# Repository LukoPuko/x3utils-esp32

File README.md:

# x3utils-esp32

A **standalone ESP32 flasher for the AT32F415 VCU** on X3-family e-scooters
(ZT3 Pro, Max G3, F3 / F3 Pro), controlled entirely from your **phone's browser
over WiFi**.

No PC. No ST-LINK. No app install. The ESP32 *is* the programmer: it bit-bangs
SWD to the scooter's debug pins itself, and hosts a web UI you drive from
Safari on an iPhone (or any browser — WiFi, so the Chrome/WebUSB limitation of
the original web app does not apply).

This is an ESP32 port of [**x3utils**](https://github.com/ztakis/x3utils). The
flashing *brains* — the AT32F415 erase/program/verify sequence, the FAP
read-protection check and rescue, the SHU-compatibility patch and its firmware
safety gates — are ported straight from the upstream engine. Only the transport
changed: an ESP32 GPIO SWD master replaces the ST-LINK, and a built-in web
server replaces the desktop GUI.

> [!WARNING]
> This tool writes the scooter VCU directly. A wrong file, a bad contact, or an
> interrupted flash can leave the controller unusable until recovered. **Always
> make a full backup first and keep it safe.** Use 3.3 V logic only, and power
> the VCU from **one** source at a time.

> [!IMPORTANT]
> **On-hardware validation status.** The firmware-identity / SHU-compat safety
> gates and the Thumb-2 version decoder are covered by host unit tests (see
> `host_test/`). The bit-banged SWD transaction layer (`swd.cpp`) follows the
> standard ADIv5 framing but has **not** been bench-verified against a real
> AT32F415 in this repository's CI (none exists). Treat your first connection as
> a bring-up: start with **Check connection** and **Backup**, confirm a clean
> 128 KB read, and only then flash. If you see `no ACK` / parity errors, raise
> the **SWD half-clock µs** setting (1–3) for a slower, more tolerant line.

---

## What it does

Same operations as the desktop/web app, from the browser:

- **Check connection** — read-only probe + target identification.
- **Backup 128 KB** — full dump, validated, downloaded to your phone as a `.bin`.
- **Backup + Flash** — upload a full 128 KB `.bin`; it erases, writes, verifies.
- **Flash slot 0** — upload a slot-0 `.bin` (identity-preserving).
- **Check protection** — read-only FAP (read-protection) verdict.
- **Unlock / Rescue** — clears FAP; this **mass-erases** main flash (recovery path).
- **Make SHU compatible** — dumps, patches the chip's own firmware at `0x1420`,
  and flashes it back. Safety-gated exactly like upstream: refuses non-factory
  firmware, XTEA-present (too-new) firmware, unsupported models (GT3), and
  blacklisted/unidentified versions.

Connection modes: **Default SWD**, **Under-reset (nRST)**, and **Power-race**
(hammer connect while you apply power).

---

## Hardware

### Option A — the X3-Tuner PCB (all-in-one)

[`hardware/`](hardware/) contains a ready-to-order board built only for this
job (documentation in German):
- **MCU:** ESP32-C3-WROOM-02 module, chosen as the cost-optimised option.
- **USB:** USB-C wired to the C3's native USB, so no USB-UART chip is needed.
- **Battery:** 1S LiPo with a TP4056 charger and DW01A protection.
- **VCU supply:** a GPIO-switched 3.3 V supply, so the firmware can run *Power-race* by itself.
- **Board:** 38 × 54.5 mm, two layers, all parts on one side.
- **Manufacturing files:** Gerber, BOM and CPL for JLCPCB assembly, plus a 10-up panel for volume orders.
- **Case:** a 3D-printable enclosure.

Build the firmware with `pio run -e x3tuner -t upload`.

### Option A2 — X3-Tuner Mini: carrier board for an ESP32-C3 SuperMini

[`hardware/carrier/`](hardware/carrier/) is a cheaper board: a ready-made
ESP32-C3 SuperMini (about 1.80 €) is pushed onto pin headers the factory solders
to the carrier and is held by the case lid. The carrier adds:
- a 1S LiPo charger with reverse-polarity protection, and an on/off switch;
- the switched VCU supply;
- battery, USB and VCU voltage sensing;
- the SWD header.

Every part is machine-assembled, nothing to solder. In volume a complete board
including the SuperMini comes to about 3.75 €. The board is a 20.5 × 65 mm
stick; with its 3D-printed case and a LiPo the device measures about
78 × 24 × 21 mm. The case is fully closed (no button holes) and the firmware can
be locked against readout with Wi-Fi-only OTA updates — see
[hardware/carrier/SECURITY.md](hardware/carrier/SECURITY.md). Build the firmware
with `pio run -e x3carrier -t upload`.

### Option B — any ESP32 dev board

- An **ESP32** board (classic ESP32, or an S3 / C3 — see `platformio.ini`).
- Four wires to the scooter's debug header: **SWCLK**, **SWDIO**, **GND**, and
  **nRST / C45** (strongly recommended — needed for Under-reset mode and most
  reliable for locked/running targets).
- A 3.3 V power path for the VCU (bench/main power **or** the ESP32 3V3 pin —
  never both). See the upstream wiki's per-model guides for pad locations and
  the C45 point.

### Default pin map (classic ESP32 — change in `src/config.h` or the UI)

| Signal | GPIO |
|--------|------|
| SWCLK  | 18   |
| SWDIO  | 19   |
| nRST   | 21   |
| GND    | any GND |

S3/C3 defaults are different — see `src/config.h`.

---

## Build & flash the ESP32

Uses [PlatformIO](https://platformio.org/).

```bash
# classic ESP32
pio run -e esp32dev -t upload

# or an S3 / C3 board
pio run -e esp32-s3 -t upload
# the X3-Tuner PCB from hardware/ (ESP32-C3, native USB)
pio run -e x3tuner -t upload
# the X3-Tuner Mini carrier from hardware/carrier/ with a plug-in SuperMini
pio run -e x3carrier -t upload
pio run -e esp32-c3 -t upload

# watch the serial log (shows the WiFi IP)
pio device monitor -b 115200
```

First boot creates a **WiFi hotspot**:

- SSID: `x3utils-esp32`  ·  password: `x3utils123`
- Join it from your phone, then open **http://192.168.4.1/** (or
  **http://x3utils.local/**).

To join your own network instead, open **Settings → WiFi → Join network** in the
UI, enter your SSID/password, and save (the ESP32 reboots and connects; find its
IP on the serial monitor or your router).

---

## Using it from your phone

1. Wire SWCLK / SWDIO / GND / nRST to the VCU, power the VCU from one source.
2. Join the ESP32 hotspot and open the page.
3. Pick a connection mode (start with **Default SWD**; use **Under-reset** if the
   firmware keeps SWD disabled while running).
4. **Check connection** → you should see the AT32F415 part identified.
5. **Backup 128 KB** → wait for "Backup complete", then **Download last backup**.
6. Only now flash: **Backup + Flash** / **Flash slot 0** (upload a `.bin`), or
   **Make SHU compatible**.

The console streams live log + progress over a WebSocket. **Abort** stops a
running operation (safe between steps; a flash in progress finishes its current
word).

---

## How the port works

The upstream engine is written against a tiny debug-probe surface — read/write a
debug register, read/write memory, drive nRST. `src/swd.cpp` provides exactly
that surface by bit-banging ADIv5 SWD on two GPIOs, so the AT32 flash algorithm
in `src/at32.cpp` is the *same* algorithm the desktop/web app runs:

```
browser ──HTTP/WebSocket──> ESP32 web server (main.cpp)
                                  │  queues one command
                                  ▼
                            x3_ops.cpp  (Check/Backup/Flash/Compat/Protection)
                                  │
                      at32.cpp (Cortex-M + AT32F415 flash)   fw_ident.cpp (SHU gates)
                                  │
                              swd.cpp  (bit-banged ADIv5 SWD)
                                  │  SWCLK / SWDIO / nRST
                                  ▼
                           AT32F415 VCU
```

The experimental SRAM flash loader from upstream is intentionally **not** ported;
this uses the field-proven direct word-write path. The SHU-compat patch,
factory-state check, XTEA gate, model allow-list, and the Thumb-2 version
blacklist/known-version decoder are ported faithfully in `src/fw_ident.cpp`.

### Source layout

```
src/
  config.h       pins, WiFi defaults, SWD timing, target geometry
  swd.{h,cpp}    bit-banged ADIv5 SWD master (the ST-LINK replacement)
  at32.{h,cpp}   Cortex-M debug + AT32F415 detect / erase / program / verify / FAP
  fw_ident.{h,cpp}  banner, factory-state, version matrix, SHU-compat gates
  x3_ops.{h,cpp} high-level operations driven by the UI
  web_ui.h       the mobile web UI (served from flash)
  main.cpp       WiFi + web server + WebSocket + routing + settings
host_test/            host unit tests for the safety gates (see below)
```

## Tests

The portable safety-critical logic has host-side unit tests (no hardware, no
ESP toolchain needed):

```bash
cd host_test
g++ -std=gnu++17 -I shim -I ../src test_fwident.cpp ../src/fw_ident.cpp -o t && ./t
```

They cover the Thumb-2 version decoder, the blacklist floor, the XTEA / factory
/ already-compatible / unidentified refusals, the MCU model requirement, and the
16-byte compat patch.

---

## Credits & license

MIT. Ported from [x3utils](https://github.com/ztakis/x3utils) (© ztakis) and its
swdart engine (© nopbxlr). See [LICENSE](LICENSE). Supported models and the
firmware version matrix mirror upstream; consult the upstream wiki for wiring,
C45 locations, and SHU-compat firmware limits.

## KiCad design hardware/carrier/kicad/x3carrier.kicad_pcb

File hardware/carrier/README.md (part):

# X3-Tuner Mini – Trägerplatine für das ESP32-C3 SuperMini

Die günstige Variante des X3-Tuners, als schmaler **Stick** mit 3D-Druck-Gehäuse
(ca. 78 × 24 × 21 mm). Den ESP32 kaufst du als fertiges **ESP32-C3 SuperMini**
(ca. 1,80 €) und **steckst ihn einfach auf**. Das SuperMini hat **keine
eingelöteten Stifte** – die sitzen auf der Trägerplatine, die Fabrik lötet sie
an, und das SuperMini wird draufgesteckt und vom Deckel festgehalten.
Die Trägerplatine bringt alles mit, was dem SuperMini fehlt:

- 1S-LiPo-Akku mit TP4056-Ladeschaltung, geladen über die USB-C-Buchse des SuperMini
- Verpolschutz für den Akku (viele Billig-Akkus haben vertauschte Kabel)
- Ein/Aus-Schiebeschalter
- schaltbare 3,3-V-Versorgung für die Scooter-VCU (Power-Race per Firmware)
- Messung von Akku, USB und VCU-Spannung
- SWD-Stiftleiste zum Scooter

**Du lötest nichts.** Die Fabrik bestückt alle Teile, auch die beiden
Stiftleisten für das SuperMini und die SWD-Stiftleiste.

> [!NOTE]
> **Geschlossenes Gehäuse, geschützte Firmware.** Es gibt keine Öffnungen für
> die RESET-/BOOT-Taster: Niemand kommt von außen an das SuperMini. Die Firmware
> kann so eingestellt werden, dass sie **nicht ausgelesen oder über USB
> umgeflasht** werden kann und Updates **nur per WLAN über deine App** laufen –
> siehe [SECURITY.md](SECURITY.md).

| Gehäuse | Durchsichtig (Aufbau) |
|---|---|
|  |  |
| **Schnitt** | **Explosionsansicht** |
|  |  |

| Platine oben | Platine unten |
|---|---|
|  |  |

[Schaltplan (PDF)](docs/x3carrier-schematic.pdf) ·
[Bestückungsplan (PDF)](docs/x3carrier-assembly.pdf) ·
[Fertigungsdaten](production/) ·
[Gehäuse (STL)](case/stl/)

> [!IMPORTANT]
> **Status: Design fertig (Rev. 1.2, Stick mit Stiftleisten), noch nicht
> gefertigt.** DRC: 0 Fehler, 0 offene Verbindungen, der Schaltplan wird
> automatisch gegen die Netzliste geprüft. Das Gehäuse ist gegen Platine,
> SuperMini und Akku auf Kollisionen geprüft. **Eine Sache fehlt noch:** die
> LCSC-Nummer der 1×8-Stiftleiste – siehe [Bestellen](#bestellen). Vor der
> Bestellung bitte [diese Punkte](#vor-der-bestellung-prüfen) prüfen.

## Was drauf ist

| Block | Lösung |
|---|---|
| Platine | 20,5 × 65 mm, 2 Lagen, alle Teile oben |
| ESP32 | ESP32-C3 SuperMini, auf 2 × 1×8-**Stiftleisten** (2,54 mm) aufgesteckt und vom Deckel niedergehalten, USB-C an der vorderen Kante |
| Laden | TP4056, ca. 235 mA, gespeist aus dem 5V-Pin des SuperMini (= USB VBUS). LEDs: rot = lädt, grün = voll |
| Akku | 1S LiPo **mit eigener Schutzschaltung**, JST-PH-2.0-Buchse, Verpolschutz (P-MOSFET Q3) |
| Ein/Aus | Schiebeschalter MSK12C02. Er schaltet nur das Gate des P-MOSFET Q1 und trägt keinen Laststrom |
| Akkubetrieb | Akku → Q3 → Q1 → Schottky-Diode D1 → 5V-Pin → 3,3-V-Regler des SuperMini |
| VCU-Versorgung | P-MOSFET Q2 aus 3V3 des SuperMini, GPIO7 low = an, beim Booten aus |
| SWD | gewinkelte 1×5-Stiftleiste an der hinteren Kante (3V3 · DIO · CLK · RST · GND), 100 Ω Serienwiderstände |

### Belegung des SuperMini

Ansicht von oben, USB-C nach oben. Pin 1 jeder Reihe ist der Pin neben USB-C.
Auf der Platine zeigt USB-C zur vorderen Kante (Aufdruck „USB-C“), die
5V-Reihe liegt dann links (Aufdruck „5V“).

| Linke Reihe | Funktion | Rechte Reihe | Funktion |
|---|---|---|---|
| 5V | Akku / Lader (= USB VBUS) | GPIO5 | SWDIO |
| GND | GND | GPIO6 | nRST |
| 3V3 | 3,3 V für die VCU | GPIO7 | VCU-Versorgung ein (low) |
| GPIO4 | SWCLK | GPIO8 | blaue LED des SuperMini (Status, im Gehäuse verdeckt) |
| GPIO3 | VCU-Spannung messen | GPIO9 | BOOT-Taster (im Gehäuse nicht erreichbar) |
| GPIO2 | frei (Strapping) | GPIO10 | frei |
| GPIO1 | USB-Erkennung | GPIO20 | frei |
| GPIO0 | Akkuspannung messen | GPIO21 | frei |

SWD liegt auf denselben Pins wie beim nackten SuperMini (Firmware-Umgebung
`esp32-c3`). Die Trägerplatine hat ein eigenes Firmware-Profil:

```bash
pio run -e x3carrier -t upload
```

### Stromversorgung

- **USB eingesteckt:** USB versorgt das SuperMini, der TP4056 lädt den Akku.
  D1 sperrt, deshalb wird der Akku nur geladen und nicht gleichzeitig belastet.
  Laden funktioniert auch bei ausgeschaltetem Schalter. Das SuperMini läuft dann
  über USB trotzdem.
- **Akku:** Schalter auf EIN, dann versorgt der Akku das SuperMini über Q3, Q1 und D1.
  Durch die Diode und den Regler des SuperMini sinkt die 3,3-V-Schiene ab etwa
  3,5 V Akkuspannung. Das Gerät geht dann früher aus als mit einem eigenen
  Regler, nutzbar sind ca. 85–90 % der Akkukapazität.
- **Aus:** Am Akku hängt nur der Messteiler mit 1 MΩ + 1 MΩ, das sind ca. 2 µA.
- **Akku verkehrt herum:** Q3 sperrt. Es geht nichts kaputt, das Gerät läuft
  nur nicht mit Akku und lädt ihn nicht.

## Akku

Ins Gehäuse passt ein Akku bis **21 × 33 × 7 mm**. Er liegt in einer Tasche
unter dem Deckel, über der Ladeschaltung. Gut passen die Größen 702030 und
602030. Die Zahl steht für Dicke, Breite und Länge: 602030 ist 6,0 × 20 × 30 mm.
Der Akku braucht eine **Schutzschaltung** und einen **JST-PH-2.0-Stecker**
(2 mm Raster). Beides ist bei Akkus mit Stecker üblich.

| Akku | Kapazität | Maße (L × B × D) | Polarität | Preis |
|---|---|---|---|---|
| [efaso 702030](https://www.amazon.de/dp/B0BK9JQY42) (Amazon.de, empfohlen) | 300 mAh | 30 × 20 × 7 mm | nicht angegeben, prüfen | ca. 9 € |
| [Pimoroni LiPo 150 mAh](https://botland.store/battery-li-pol-1s-37-v/21461-li-pol-battery-pimoroni-150mah-37v-jst-connector-27x205x43mm-0704256796549.html) | 150 mAh | 27 × 20,5 × 4,3 mm | passt garantiert (Adafruit-Belegung) | ca. 6 € |
| [Berrybase LP-402025](https://www.berrybase.de/en/lp-402025-lithium-polymer-lipo-battery-3.7v-150mah-with-2-pin-jst-connector) | 150 mAh | 26 × 20 × 4 mm | nicht angegeben, prüfen | ca. 3,30 € |

Die Akkutasche ist für Zellen bis **7 mm** Dicke ausgelegt. Ein dickerer 8-mm-Akku
(z. B. ein 802030, 400 mAh) würde sonst an die JST-Buchse stoßen; dafür den
Deckel 2 mm höher bauen (`CASE_TOP_CLEAR` in [`../gen/circuit_carrier.py`](../gen/circuit_carrier.py)
auf 15 setzen und neu rendern).

Mit 300 mAh läuft das Gerät mit WLAN ca. 2–3 Stunden, mit 150 mAh gut eine
Stunde. Für einen Flash-Vorgang reicht beides. Der Ladestrom von ca. 235 mA
passt gut zu 300 mAh. Für die 150-mAh-Akkus ist er etwas hoch (1,5C), sie altern
dadurch schneller.

**Zwei kleine Akkus parallel** sind keine gute Idee: Sind sie beim Zusammenstecken
unterschiedlich voll, fließt ein großer Ausgleichsstrom, den nichts begrenzt.
Außerdem bräuchtest du ein Y-Kabel, und das müsste man löten. Ein einzelner
702030 hat mehr Kapazität als zwei 150-mAh-Zellen und passt in dasselbe Fach.

**Polarität:** Die Platine hat die Belegung von Adafruit und SparkFun:
**+ (rot) an Pin 1**. Schau in die Öffnung der Buchse, die Platine liegt unten.
Dann ist + **links**, daneben steht „+“ auf der Platine. Am Akkustecker gilt:
Schau auf die Kontaktöffnungen, die Rastnase zeigt nach oben. Dann muss Rot
**rechts** sein. Bei Akkus von Amazon und AliExpress ist das oft vertauscht.
Steckst du so einen Akku an, sperrt der Verpolschutz und es passiert nichts.
Umbauen geht auch ohne Löten: Hebe mit einer Nadel die kleine Rastzunge über
einem Kontakt im Steckergehäuse an. Dann kannst du das Kabel samt Kontakt
herausziehen. Beide Kabel tauschen und wieder einrasten.

## Gehäuse

Facettierter Stick aus zwei Teilen, die ohne Schrauben einrasten.
Außenmaß **77,7 × 24,4 × 20,9 mm**. Die Oberseite ist geschlossen, nur die
Lade-LED zeigt sich durch einen schmalen Schlitz. Es nutzt dasselbe Modell wie
das [X3-Tuner-Gehäuse](../case/) ([`../case/case_core.scad`](../case/case_core.scad)).

| Ebene | Höhe |
|---|---|
| Boden | 1,2 mm |
| Luft für die Lötbeine der Stiftleisten (THT) | 3,2 mm |
| Platine | 1,6 mm |
| SuperMini auf den Stiftleisten (2,5 mm) + Luft, Akku im Deckel (bis 8 mm) | 13,5 mm |
| Deckel | 1,4 mm |
| **Gesamt** | **20,9 mm** |

Weil das SuperMini jetzt flach auf den Stiftleisten sitzt (statt auf hohen
Buchsen), bestimmt der **Akku im Deckel** die Höhe. Mit einem 7-mm-Akku bleibt
es bei 20,9 mm.

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
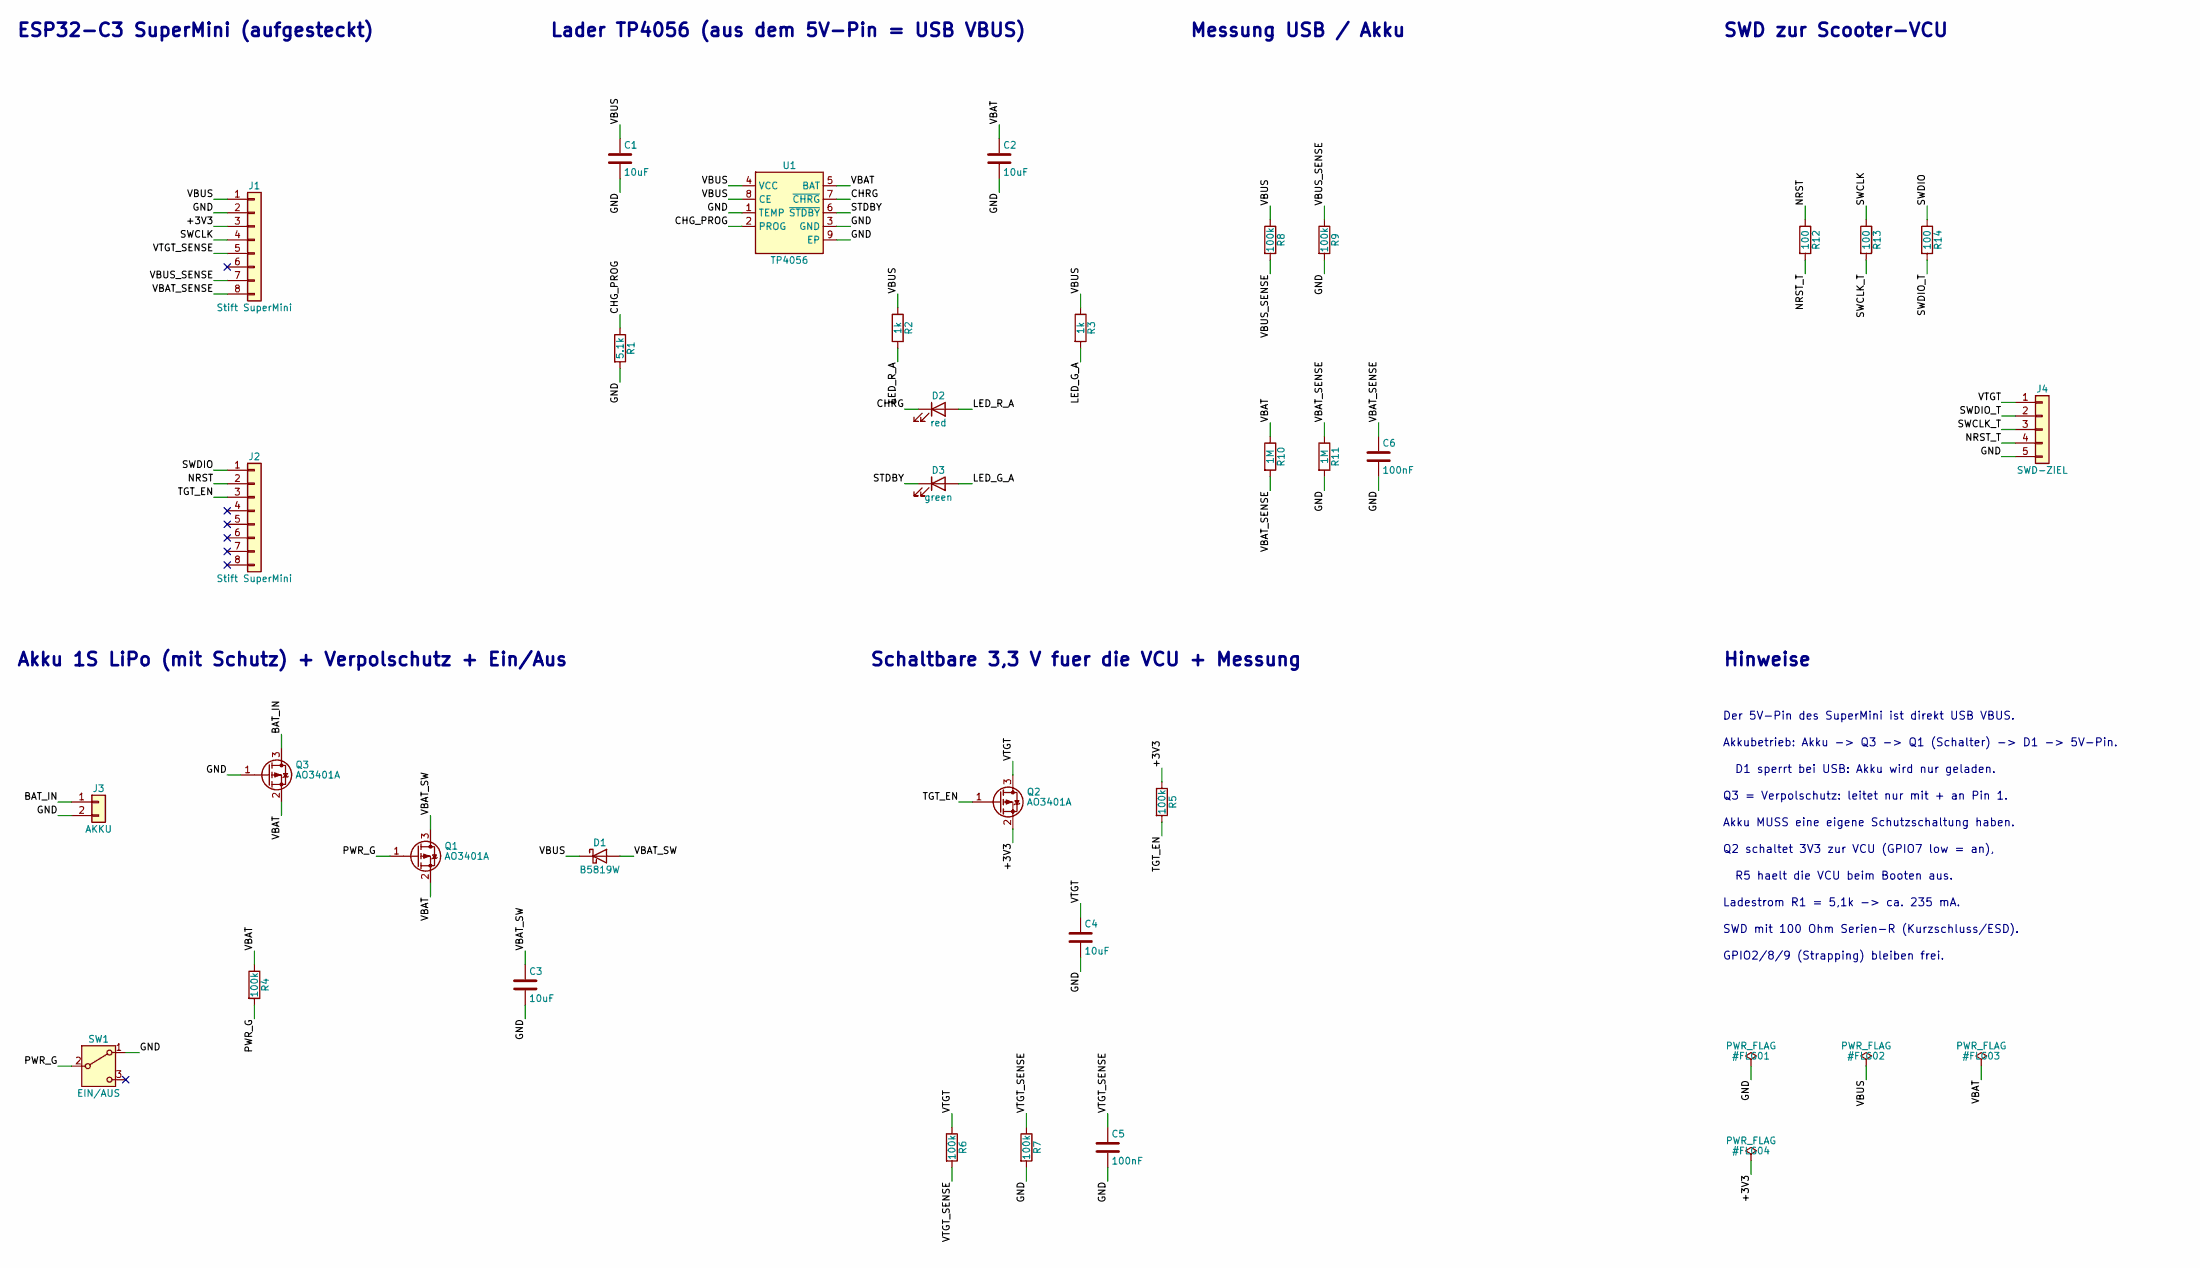
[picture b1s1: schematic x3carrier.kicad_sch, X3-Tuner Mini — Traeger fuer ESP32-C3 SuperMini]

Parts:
C1, C2, C3, C4: 10uF; C_0603_1608Metric; LCSC C19702
C5, C6: 100nF; C_0402_1005Metric; LCSC C1525
D1: B5819W; D_SOD-123; LCSC C8598
D2: red; LED_0603_1608Metric; LCSC C2286
D3: green; LED_0805_2012Metric; LCSC C2297
J1, J2: Stift SuperMini; PinHeader_1x08_P2.54mm_Vertical
J3: AKKU; JST_PH_S2B-PH-SM4-TB_1x02-1MP_P2.00mm_Horizontal; LCSC C295747
J4: SWD-ZIEL; PinHeader_1x05_P2.54mm_Horizontal; LCSC C32713264
Q1, Q2, Q3: AO3401A; SOT-23; LCSC C15127
R1: 5.1k; R_0402_1005Metric; LCSC C25905
R2, R3: 1k; R_0402_1005Metric; LCSC C11702
R4, R5, R6, R7, R8, R9: 100k; R_0402_1005Metric; LCSC C25741
R10, R11: 1M; R_0402_1005Metric; LCSC C26083
R12, R13, R14: 100; R_0402_1005Metric; LCSC C25076
SW1: EIN/AUS; SW_SPDT_MSK12C02; LCSC C431540
U1: TP4056; SOIC-8-1EP_3.9x4.9mm_P1.27mm_EP2.41x3.3mm; LCSC C16581

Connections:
+3V3: J1.3, Q2.2 (S), R5.1
BAT_IN: J3.1, Q3.3 (D)
CHG_PROG: R1.1, U1.2 (PROG)
CHRG: D2.1 (K), U1.7 (~CHRG)
GND: C1.2, C2.2, C3.2, C4.2, C5.2, C6.2, J1.2, J3.2, J4.5, Q3.1 (G), R1.2, R7.2, R9.2, R11.2, SW1.1 (A), U1.1 (TEMP), U1.3 (GND), U1.9 (EP)
LED_G_A: D3.2 (A), R3.2
LED_R_A: D2.2 (A), R2.2
NRST: J2.2, R12.1
NRST_T: J4.4, R12.2
PWR_G: Q1.1 (G), R4.2, SW1.2 (B)
STDBY: D3.1 (K), U1.6 (~STDBY)
SWCLK: J1.4, R13.1
SWCLK_T: J4.3, R13.2
SWDIO: J2.1, R14.1
SWDIO_T: J4.2, R14.2
TGT_EN: J2.3, Q2.1 (G), R5.2
VBAT: C2.1, Q1.2 (S), Q3.2 (S), R4.1, R10.1, U1.5 (BAT)
VBAT_SENSE: C6.1, J1.8, R10.2, R11.1
VBAT_SW: C3.1, D1.2 (A), Q1.3 (D)
VBUS: C1.1, D1.1 (K), J1.1, R2.1, R3.1, R8.1, U1.4 (VCC), U1.8 (CE)
VBUS_SENSE: J1.7, R8.2, R9.1
VTGT: C4.1, J4.1, Q2.3 (D), R6.1
VTGT_SENSE: C5.1, J1.5, R6.2, R7.1

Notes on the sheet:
ESP32-C3 SuperMini (aufgesteckt)
Lader TP4056 (aus dem 5V-Pin = USB VBUS)
Akku 1S LiPo (mit Schutz) + Verpolschutz + Ein/Aus
Schaltbare 3,3 V fuer die VCU + Messung
Messung USB / Akku
SWD zur Scooter-VCU
Hinweise
Der 5V-Pin des SuperMini ist direkt USB VBUS.
Akkubetrieb: Akku -> Q3 -> Q1 (Schalter) -> D1 -> 5V-Pin.
D1 sperrt bei USB: Akku wird nur geladen.
Q3 = Verpolschutz: leitet nur mit + an Pin 1.
Akku MUSS eine eigene Schutzschaltung haben.
Q2 schaltet 3V3 zur VCU (GPIO7 low = an),
R5 haelt die VCU beim Booten aus.
Ladestrom R1 = 5,1k -> ca. 235 mA.
SWD mit 100 Ohm Serien-R (Kurzschluss/ESD).
GPIO2/8/9 (Strapping) bleiben frei.

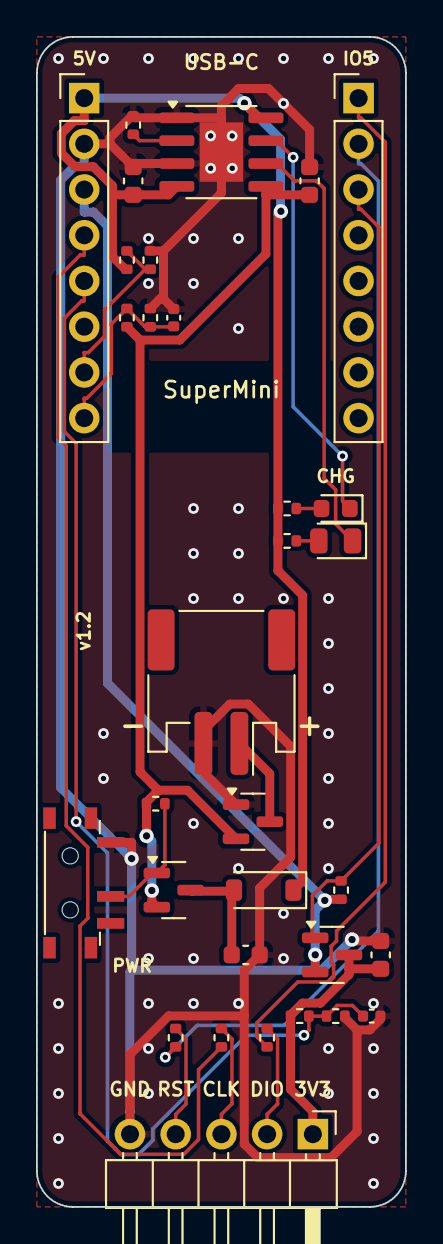
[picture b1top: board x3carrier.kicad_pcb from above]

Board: 2 copper layers, 20.5 x 65.0 mm, 39 parts (0 on the bottom side), 23 nets.

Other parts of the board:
KT1, KT2, KT3, KT4, KT5, KT6, KT7: Tab

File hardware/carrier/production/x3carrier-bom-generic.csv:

Designator,Qty,Value,Package,Manufacturer,MPN,LCSC,Description
"C1,C2,C3,C4",4,10uF,C_0603_1608Metric,,,C19702,"MLCC X5R/X7R, >= 10 V"
"C5,C6",2,100nF,C_0402_1005Metric,,,C1525,"MLCC X5R/X7R, >= 10 V"
D1,1,B5819W,D_SOD-123,CJ,B5819W SL,C8598,"Akku -> 5V-Pin, sperrt bei USB"
D2,1,red,LED_0603_1608Metric,KENTO,KT-0603R,C2286,LED rot = lädt
D3,1,green,LED_0805_2012Metric,KENTO,KT-0805G,C2297,LED grün = voll
"J1,J2",2,Stift SuperMini,PinHeader_1x08_P2.54mm_Vertical,,"Stiftleiste 1x8 2,54 mm THT (LCSC-Nr. ergaenzen)",,"Stiftleiste 1x8 2,54 mm fuer ESP32-C3 SuperMini (aufgesteckt)"
J3,1,AKKU,JST_PH_S2B-PH-SM4-TB_1x02-1MP_P2.00mm_Horizontal,JST,S2B-PH-SM4-TB(LF)(SN),C295747,"LiPo 1S mit Schutzschaltung, JST-PH 2.0, + = Pin 1"
J4,1,SWD-ZIEL,PinHeader_1x05_P2.54mm_Horizontal,hanxia,"HX PZ2.54-1x5P WZ (1x5 2.54 mm, gewinkelt, THT)",C32713264,Stiftleiste 1x5 gewinkelt zum Scooter (3V3 DIO CLK RST GND)
"Q1,Q2,Q3",3,AO3401A,SOT-23,AOS,AO3401A,C15127,Verpolschutz Akku (P-MOSFET)
R1,1,5.1k,R_0402_1005Metric,,,C25905,"Widerstand 1 %, Dickschicht"
"R2,R3",2,1k,R_0402_1005Metric,,,C11702,"Widerstand 1 %, Dickschicht"
"R4,R5,R6,R7,R8,R9",6,100k,R_0402_1005Metric,,,C25741,"Widerstand 1 %, Dickschicht"
"R10,R11",2,1M,R_0402_1005Metric,,,C26083,"Widerstand 1 %, Dickschicht"
"R12,R13,R14",3,100,R_0402_1005Metric,,,C25076,"Widerstand 1 %, Dickschicht"
SW1,1,EIN/AUS,SW_SPDT_MSK12C02,SHOU HAN,MSK12C02,C431540,Schiebeschalter Ein/Aus
U1,1,TP4056,SOIC-8-1EP_3.9x4.9mm_P1.27mm_EP2.41x3.3mm,TOPPOWER,TP4056-42-ESOP8,C16581,"Li-Ion Lader 1S, ~235 mA"

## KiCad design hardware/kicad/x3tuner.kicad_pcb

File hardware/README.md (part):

# X3-Tuner – eigene Platine für x3utils-esp32

Ein **All-in-one-Gerät** für die AT32F415-VCU der X3-Scooter-Familie (ZT3 Pro,
Max G3, F3 / F3 Pro): ESP32-C3 (Spar-Version), eigener Akku mit Lade- und
Schutzschaltung, schaltbare 3,3-V-Versorgung für die VCU und ein SWD-Stecker.
Ersetzt **ST-LINK, PC und Kabelsalat** – bedient wird alles per Handy-Browser
über WLAN (Firmware: dieses Repository, Environment `x3tuner`).

| Oberseite | Unterseite |
|---|---|
|  |  |

[Schaltplan (PDF)](docs/x3tuner-schematic.pdf) ·
[Bestückungsplan (PDF)](docs/x3tuner-assembly.pdf) ·
[Fertigungsdaten](production/) ·
[3D-Druck-Gehäuse](case/)

> [!TIP]
> **Noch günstiger: [X3-Tuner Mini](carrier/)**. Das ist eine Trägerplatine, auf die ein fertiges
> ESP32-C3 SuperMini (ca. 1,80 €) nur aufgesteckt wird (Stiftleisten bestückt die Fabrik). Akku,
> Laden, Schalter und SWD sind drauf, alles wird bestückt. In Serie kostet ein Gerät damit ca.
> 3,75 € statt 5,40 €. Mit Gehäuse ist es ein geschlossener Stick von ca. 78 × 24 × 21 mm; die
> Firmware lässt sich gegen Auslesen sperren (nur WLAN-OTA, siehe [carrier/SECURITY.md](carrier/SECURITY.md)).

> [!IMPORTANT]
> **Status: Design fertig (Rev. 1.1, Spar-Version mit ESP32-C3), noch nicht gefertigt.** Die Platine besteht den
> KiCad-DRC (0 Fehler, 0 offene Verbindungen) und der Schaltplan wird
> automatisch gegen die Netzliste geprüft – ein gebauter Prototyp existiert
> aber noch nicht. Bitte zuerst **2–5 Stück** bestellen und testen. Was du vor
> der Bestellung prüfen solltest, steht unter [Vor der Bestellung prüfen](#vor-der-bestellung-prüfen).

---

## Was drauf ist

| Block | Lösung | Warum |
|---|---|---|
| MCU | **ESP32-C3-WROOM-02-N4**: 4 MB Flash, 400 KB RAM, WLAN + BLE | ca. 1,20–1,55 $ günstiger als der S3; die Firmware braucht nur 128 KB Puffer |
| USB | USB-C direkt an GPIO18/19 (natives USB des C3) | kein CH340/CP2102 nötig → günstiger |
| Laden | **TP4056**, ca. 360 mA (R4 = 3,3 kΩ), LEDs rot = lädt, grün = voll | Standard, sehr billig |
| Akku-Schutz (BMS) | **DW01A + 8205-Dual-MOSFET** | Schutz vor Über- und Tiefentladung, Überstrom und Kurzschluss |
| Power-Path | P-MOSFET AO3401A + Schottky B5819W | mit USB läuft das Gerät aus USB, der Akku wird nur geladen |
| 3,3 V ESP | ME6211 (500 mA LDO), Ein/Aus-Schiebeschalter **MSK12C02** am Enable-Pin | kleiner Ruhestrom, Laden auch im ausgeschalteten Zustand; Schalter ca. 0,05 $ |
| 3,3 V VCU | **zweiter ME6211, per GPIO10 schaltbar**, mit Spannungsmessung | Firmware schaltet die VCU selbst ein → **automatischer Power-Race** |
| SWD | 1×5-Stiftleiste 2,54 mm (3V3 · DIO · CLK · RST · GND), 100 Ω Serienwiderstände | Dupont-Kabel wie beim ST-LINK |
| Bedienung | RESET, BOOT, Status-LED (weiß) | |
| Messung | Akkuspannung, USB vorhanden, Spannung an der VCU (alle ADC1) | Akkuanzeige in der Web-Oberfläche, Schutz gegen Doppelversorgung |

**Platine:** 38 × 54,5 mm, 2 Lagen, 1,6 mm, alle Teile auf der Oberseite
(einseitige Bestückung = günstig). JLC bestückt **alles**, auch die
SWD-Stiftleiste – von Hand gelötet wird nichts. Unten durchgehende Massefläche – dort klebt
der Akku. Antenne am oberen Rand, ohne Kupfer darunter.

### Pinbelegung ESP32-C3-WROOM-02

| GPIO | Funktion | | GPIO | Funktion |
|---|---|---|---|---|
| IO5 | SWCLK (über 100 Ω) | | IO3 | VTGT_SENSE (Spannung an der VCU, ½) |
| IO6 | SWDIO (über 100 Ω) | | IO1 | VBUS_SENSE (USB steckt, ½) |
| IO7 | nRST (zur VCU, über 100 Ω) | | IO4 | VBAT_SENSE (Akkuspannung, ½) |
| IO10 | TGT_EN (VCU-Versorgung ein) | | IO0 | Status-LED |
| IO9 | BOOT-Taste | | IO18/19 | USB D−/D+ |
| EN | RESET-Taste | | IO20/21 | UART0 (Testpads TP2/TP1) |
| IO2, IO8 | Strapping-Pins, je 10 kΩ nach 3,3 V | | | |

Die SWD-Pins liegen links am Modul, auf der Seite des Steckers. Alle
Messeingänge sind ADC1, denn ADC2 funktioniert beim C3 nicht, solange WLAN läuft.

### SWD-Stecker J3 (von links nach rechts, Oberseite)

| GND | RST | CLK | DIO | 3V3 |
|---|---|---|---|---|
| Masse | nRST / C45 | SWCLK | SWDIO | 3,3 V **vom Gerät** (schaltbar) – oder Messeingang, wenn die VCU anders versorgt wird |

> [!WARNING]
> Die 3V3-Leitung ist ein **Ausgang**. Hängt die VCU schon an Fahrakku oder
> Netzteil, schaltet die Firmware die eigene Versorgung **nicht** ein (sie misst
> die Spannung vorher). Trotzdem gilt wie beim ST-LINK: immer nur **eine**
> Stromquelle für die VCU.

### Bedienelemente

| Teil | Funktion |
|---|---|
| Schiebeschalter (links, „PWR") | Gerät ein/aus. Geladen wird auch im ausgeschalteten Zustand. |
| RESET (rechts) | ESP32 neu starten |
| BOOT (links) | beim Reset halten = Download-Modus (nur bei „verflashter" Firmware nötig) |
| LED „CHG" rot / grün | lädt / voll (TP4056) |
| LED „STAT" weiß | kurzes Blitzen alle 2 s = bereit, schnelles Blinken = Vorgang läuft |

---

### Warum ein fertiges Modul und kein nackter ESP32-C3-Chip?

Live-Preise von jlcpcb.com, Stand 6.10.2026, jeweils der 1+-Preis:

| | WROOM-02 (Modul) | nackter Chip ESP32-C3FH4 |
|---|---|---|
| Funkchip | 3,29 $ (alles drin) | 2,09 $ |
| 40-MHz-Quarz | im Modul | 0,11 $, *Extended* (kein Basic-Quarz mit 40 MHz) |
| Antenne | im Modul | Leiterbahn-Antenne; Chip-Antennen bei JLC nicht auf Lager |
| HF-Anpassung (Spule 2,7 nH + Kondensator 1,8 pF) | im Modul | je *Extended* |
| **Teile pro Platine** | **3,29 $** | **≈ 2,25 $** |
| Extended-Gebühren pro Auftrag | 3 $ | 12 $ (Chip, Quarz, Spule, Kondensator) |
| Funkzulassung (CE/RED) | Modul ist zertifiziert, Funkprüfberichte nutzbar | eigene Funkprüfung im Labor, ca. 3.000–8.000 € |
| Platine | 2 Lagen reichen | Espressif empfiehlt 4 Lagen und 50-Ω-Leitungen. Die Antenne muss mit einem Netzwerkanalysator abgestimmt werden |

Der nackte Chip spart ca. 1 $ pro Platine, kostet aber 9 $ mehr Gebühren pro
Auftrag. Bei 5 Platinen wird es dadurch **teurer**, erst ab ca. 10 Stück gleicht
sich das aus. Für ein Gerät, das verkauft werden soll, kommt die eigene
Funkprüfung dazu. Sie lohnt sich erst bei vielen tausend Stück. Deshalb bleibt es beim Modul.
Das kleinere ESP32-C3-MINI-1 kostet 3,03 $, also nur 0,26 $ weniger, braucht aber ein neues Layout.

## Akku

* **1S-LiPo 3,7 V mit JST-PH-2,0-Stecker**, Bauform **503040** (≈ 30 × 40 × 5 mm,
  ~600 mAh). Er passt unter die Platine und ins Gehäuse. Laufzeit ca. 4–6 h WLAN-Betrieb
  (der C3 braucht weniger Strom als der S3). Größer als 34 × 43 mm passt nicht
  mehr unter die 54,5-mm-Platine.
* Ladestrom ist mit R4 = 3,3 kΩ auf ~360 mA eingestellt → Akku **≥ 400 mAh**.
  Für kleinere Akkus R4 vergrößern (4,7 kΩ ≈ 255 mA, 10 kΩ ≈ 120 mA).
* ⚠️ **Polarität prüfen!** Bei JST-PH-Akkus ist die Belegung nicht einheitlich.
  Auf der Platine: **„+" = Pin 1 = links**, „−" = rechts (siehe Aufdruck).
  Falsch herum zerstört den Lader. Notfalls die Crimpkontakte im Stecker umstecken.

---

## Wo fertigen lassen? (Platine + Bestückung, Lieferung nach Deutschland)

### JLCPCB – Live-Preise vom 6. Oktober 2026

Alle Bauteilpreise, Lagerbestände, der Platinenpreis und der Versand stammen
direkt von jlcpcb.com, die Gebühren aus JLCs Hilfe-Artikeln
([PCB Assembly Price](https://jlcpcb.com/help/article/pcb-assembly-price),
[PCB Assembly FAQs](https://jlcpcb.com/help/article/pcb-assembly-faqs)).
Die Bestückungszeilen zeigt JLC erst nach dem Hochladen von BOM und CPL im
eingeloggten Warenkorb. Sie sind hier deshalb mit diesen Preisen nachgerechnet,
inklusive der Mindest- und Ausschussmengen pro Bauteil. JLC bestückt **alle**
Teile, du lötest nichts selbst.

| Economic-Bestückung, alles bestückt | 2 Stück | 5 Stück |
|---|---|---|
| Bauteile | 13,20 $ | 27,59 $ |
| Einrichtung 8,18 $ + Schablone 1,53 $ | 9,71 $ | 9,71 $ |
| Extended-Gebühr: 10 Sorten × 3 $ | 30,00 $ | 30,00 $ |
| Handlöten der Stiftleiste J3 (THT, pro Auftrag) | 3,58 $ | 3,58 $ |
| Lötstellen (0,0016 $ pro Lötstelle) | 0,61 $ | 1,52 $ |
| **Bestückung netto** | **57,10 $** | **72,40 $** |
| Platine (5 Stück, 2 Lagen, HASL) | 4,00 $ | 4,00 $ |
| Versand „Global Standard Direct Line" (8–13 Tage) | 6,41 $ | 6,41 $ |
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
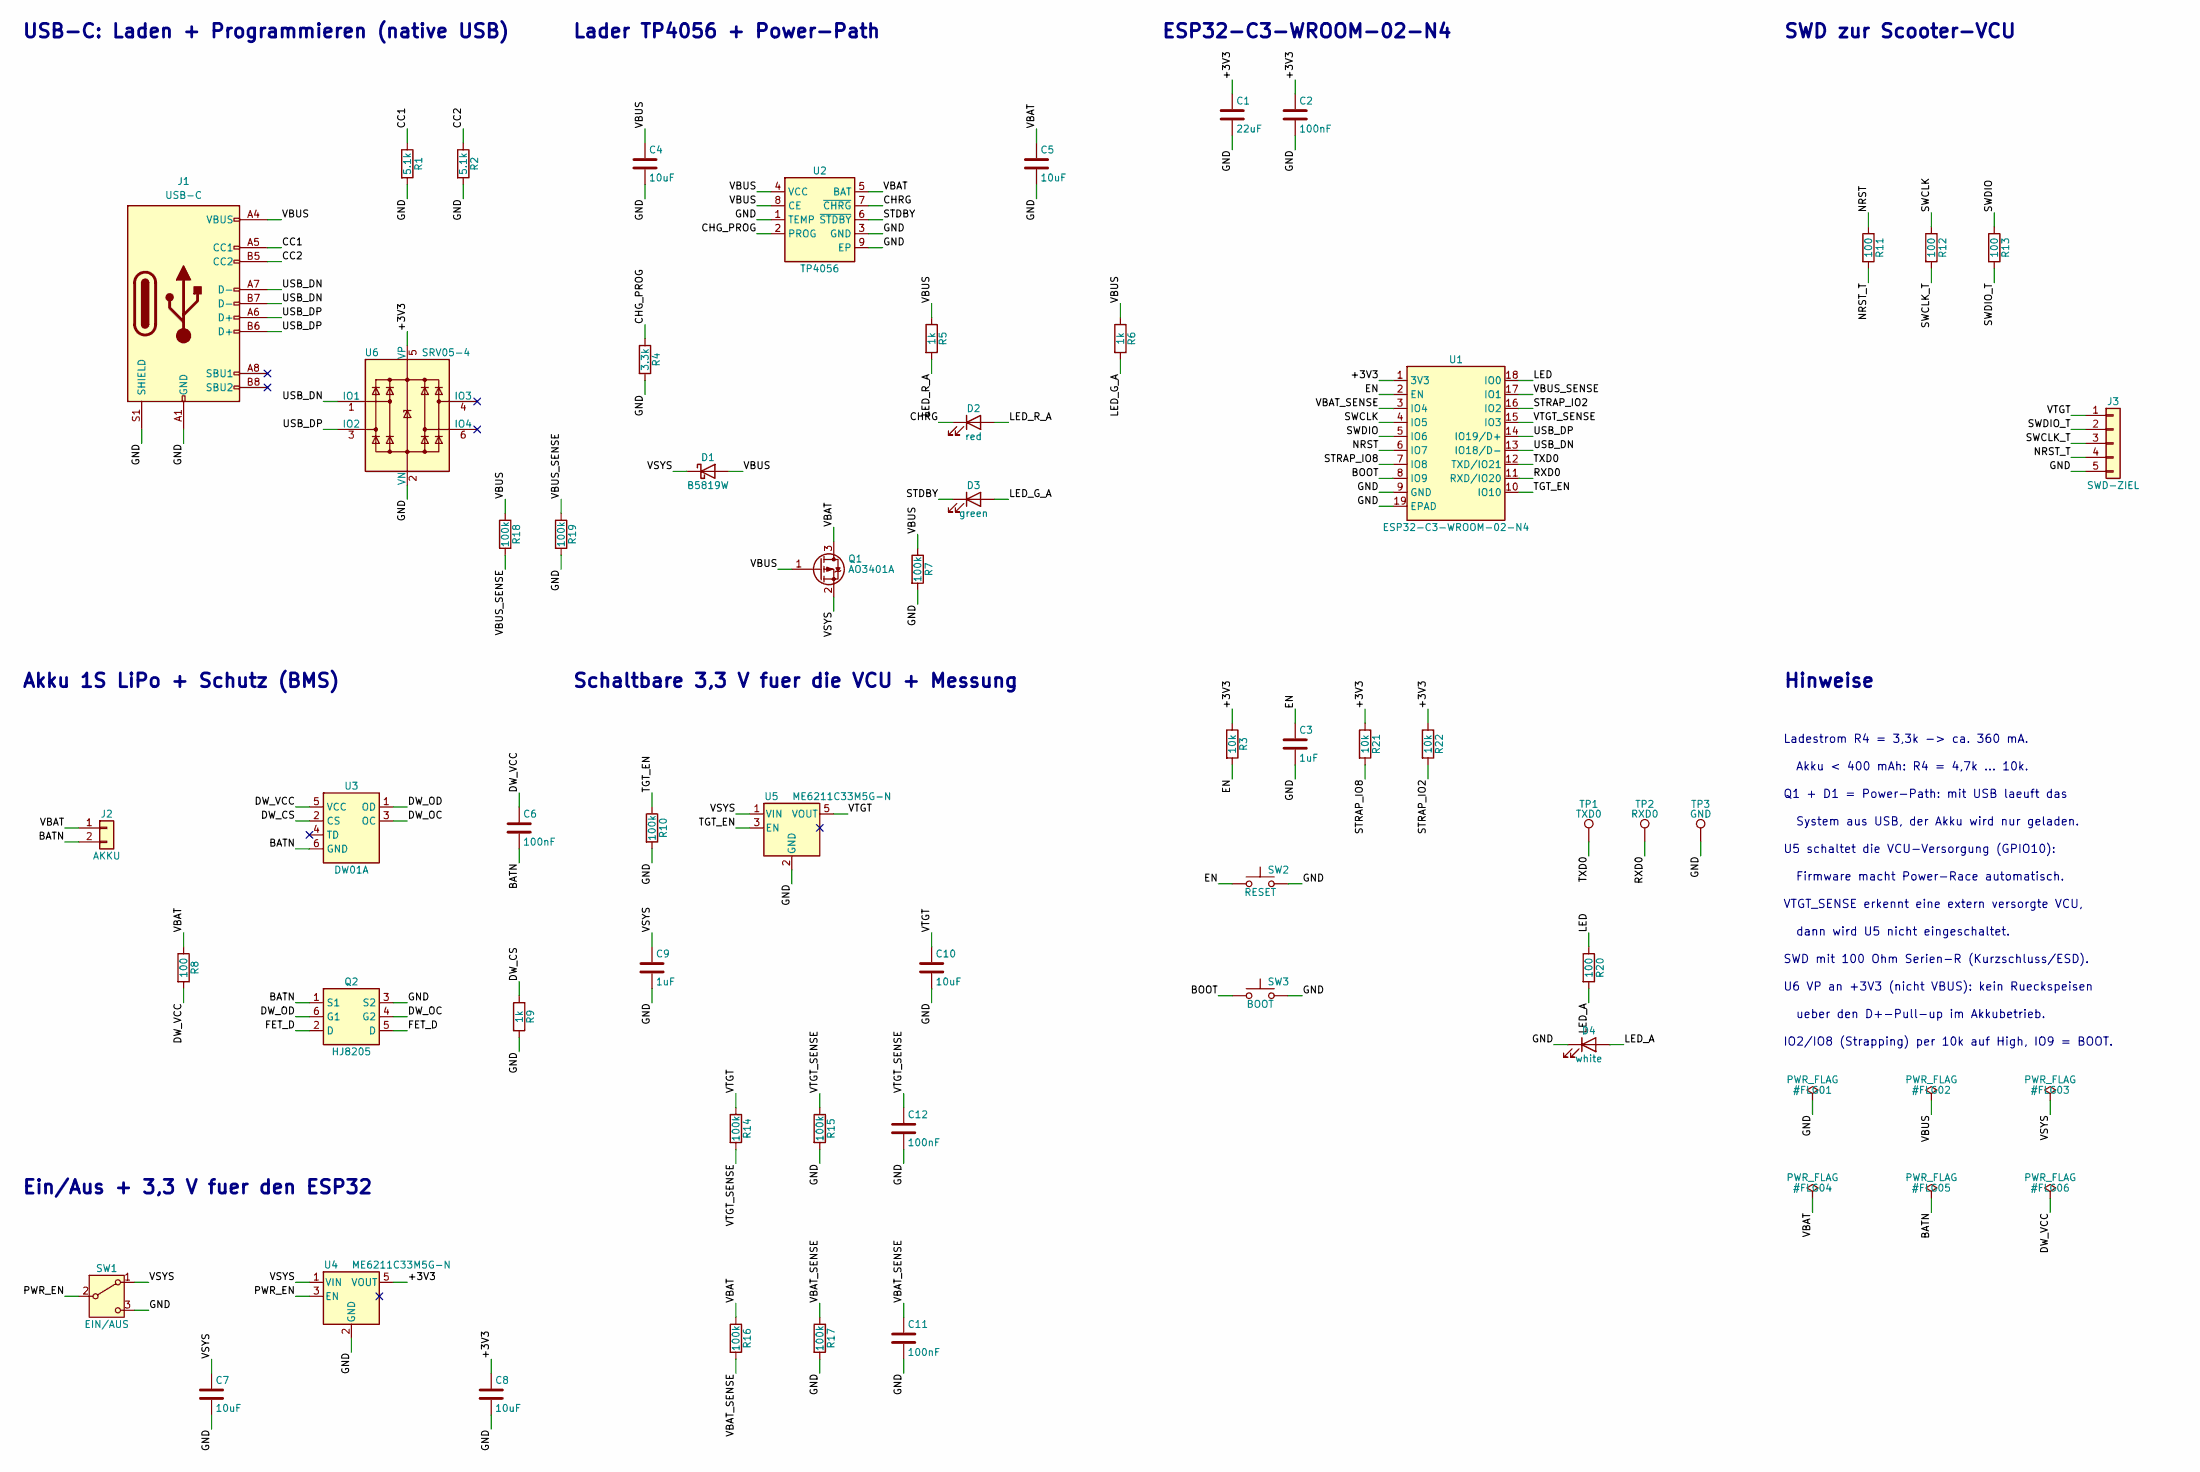
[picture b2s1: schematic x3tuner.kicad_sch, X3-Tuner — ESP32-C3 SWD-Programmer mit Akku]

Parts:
C1: 22uF; C_0805_2012Metric; LCSC C45783
C2, C6, C11, C12: 100nF; C_0402_1005Metric; LCSC C1525
C3, C9: 1uF; C_0402_1005Metric; LCSC C52923
C4, C5, C7, C8, C10: 10uF; C_0603_1608Metric; LCSC C19702
D1: B5819W; D_SOD-123; LCSC C8598
D2: red; LED_0603_1608Metric; LCSC C2286
D3: green; LED_0805_2012Metric; LCSC C2297
D4: white; LED_0603_1608Metric; LCSC C2290
J1: USB-C; USB_C_Receptacle_HRO_TYPE-C-31-M-12; LCSC C165948
J2: AKKU; JST_PH_S2B-PH-SM4-TB_1x02-1MP_P2.00mm_Horizontal; LCSC C295747
J3: SWD-ZIEL; PinHeader_1x05_P2.54mm_Horizontal; LCSC C32713264
Q1: AO3401A; SOT-23; LCSC C15127
Q2: HJ8205; SOT-23-6; LCSC C20069150
R1, R2: 5.1k; R_0402_1005Metric; LCSC C25905
R3, R21, R22: 10k; R_0402_1005Metric; LCSC C25744
R4: 3.3k; R_0402_1005Metric; LCSC C25890
R5, R6, R9: 1k; R_0402_1005Metric; LCSC C11702
R7, R10, R14, R15, R16, R17, R18, R19: 100k; R_0402_1005Metric; LCSC C25741
R8, R11, R12, R13, R20: 100; R_0402_1005Metric; LCSC C25076
SW1: EIN/AUS; SW_SPDT_MSK12C02; LCSC C431540
SW2: RESET; SW_Push_1P1T_XKB_TS-1187A; LCSC C318884
SW3: BOOT; SW_Push_1P1T_XKB_TS-1187A; LCSC C318884
TP1: TXD0; TestPoint_Pad_1.0x1.0mm
TP2: RXD0; TestPoint_Pad_1.0x1.0mm
TP3: GND; TestPoint_Pad_1.0x1.0mm
U1: ESP32-C3-WROOM-02-N4; ESP32-C3-WROOM-02_JLC; LCSC C2934560
U2: TP4056; SOIC-8-1EP_3.9x4.9mm_P1.27mm_EP2.41x3.3mm; LCSC C16581
U3: DW01A; SOT-23-6; LCSC C351410
U4, U5: ME6211C33M5G-N; SOT-23-5; LCSC C82942
U6: SRV05-4; SOT-23-6; LCSC C558418

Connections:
+3V3: C1.1, C2.1, C8.1, R3.1, R21.1, R22.1, U1.1 (3V3), U4.5 (VOUT), U6.5 (VP)
BATN: C6.2, J2.2, Q2.1 (S1), U3.6 (GND)
BOOT: SW3.1, U1.8 (IO9)
CC1: J1.A5 (CC1), R1.1
CC2: J1.B5 (CC2), R2.1
CHG_PROG: R4.1, U2.2 (PROG)
CHRG: D2.1 (K), U2.7 (~CHRG)
DW_CS: R9.1, U3.2 (CS)
DW_OC: Q2.4 (G2), U3.3 (OC)
DW_OD: Q2.6 (G1), U3.1 (OD)
DW_VCC: C6.1, R8.2, U3.5 (VCC)
EN: C3.1, R3.2, SW2.1, U1.2 (EN)
FET_D: Q2.2 (D), Q2.5 (D)
GND: C1.2, C2.2, C3.2, C4.2, C5.2, C7.2, C8.2, C9.2, C10.2, C11.2, C12.2, D4.1 (K), J1.A1 (GND), J1.A12 (GND), J1.B1 (GND), J1.B12 (GND), J1.S1 (SHIELD), J3.5, Q2.3 (S2), R1.2, R2.2, R4.2, R7.2, R9.2, R10.2, R15.2, R17.2, R19.2, SW1.3 (C), SW2.2, SW3.2, TP3.1, U1.9 (GND), U1.19 (EPAD), U2.1 (TEMP), U2.3 (GND), U2.9 (EP), U4.2 (GND), U5.2 (GND), U6.2 (VN)
LED: R20.1, U1.18 (IO0)
LED_A: D4.2 (A), R20.2
LED_G_A: D3.2 (A), R6.2
LED_R_A: D2.2 (A), R5.2
NRST: R11.1, U1.6 (IO7)
NRST_T: J3.4, R11.2
PWR_EN: SW1.2 (B), U4.3 (EN)
RXD0: TP2.1, U1.11 (RXD/IO20)
STDBY: D3.1 (K), U2.6 (~STDBY)
STRAP_IO2: R22.2, U1.16 (IO2)
STRAP_IO8: R21.2, U1.7 (IO8)
SWCLK: R12.1, U1.4 (IO5)
SWCLK_T: J3.3, R12.2
SWDIO: R13.1, U1.5 (IO6)
SWDIO_T: J3.2, R13.2
TGT_EN: R10.1, U1.10 (IO10), U5.3 (EN)
TXD0: TP1.1, U1.12 (TXD/IO21)
USB_DN: J1.A7 (D-), J1.B7 (D-), U1.13 (IO18/D-), U6.1 (IO1)
USB_DP: J1.A6 (D+), J1.B6 (D+), U1.14 (IO19/D+), U6.3 (IO2)
VBAT: C5.1, J2.1, Q1.3 (D), R8.1, R16.1, U2.5 (BAT)
VBAT_SENSE: C11.1, R16.2, R17.1, U1.3 (IO4)
VBUS: C4.1, D1.2 (A), J1.A4 (VBUS), J1.A9 (VBUS), J1.B4 (VBUS), J1.B9 (VBUS), Q1.1 (G), R5.1, R6.1, R7.1, R18.1, U2.4 (VCC), U2.8 (CE)
VBUS_SENSE: R18.2, R19.1, U1.17 (IO1)
VSYS: C7.1, C9.1, D1.1 (K), Q1.2 (S), SW1.1 (A), U4.1 (VIN), U5.1 (VIN)
VTGT: C10.1, J3.1, R14.1, U5.5 (VOUT)
VTGT_SENSE: C12.1, R14.2, R15.1, U1.15 (IO3)

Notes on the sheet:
USB-C: Laden + Programmieren (native USB)
Lader TP4056 + Power-Path
Akku 1S LiPo + Schutz (BMS)
Ein/Aus + 3,3 V fuer den ESP32
Schaltbare 3,3 V fuer die VCU + Messung
ESP32-C3-WROOM-02-N4
SWD zur Scooter-VCU
Hinweise
Ladestrom R4 = 3,3k -> ca. 360 mA.
Akku < 400 mAh: R4 = 4,7k ... 10k.
Q1 + D1 = Power-Path: mit USB laeuft das
System aus USB, der Akku wird nur geladen.
U5 schaltet die VCU-Versorgung (GPIO10):
Firmware macht Power-Race automatisch.
VTGT_SENSE erkennt eine extern versorgte VCU,
dann wird U5 nicht eingeschaltet.
SWD mit 100 Ohm Serien-R (Kurzschluss/ESD).
U6 VP an +3V3 (nicht VBUS): kein Rueckspeisen
ueber den D+-Pull-up im Akkubetrieb.
IO2/IO8 (Strapping) per 10k auf High, IO9 = BOOT.

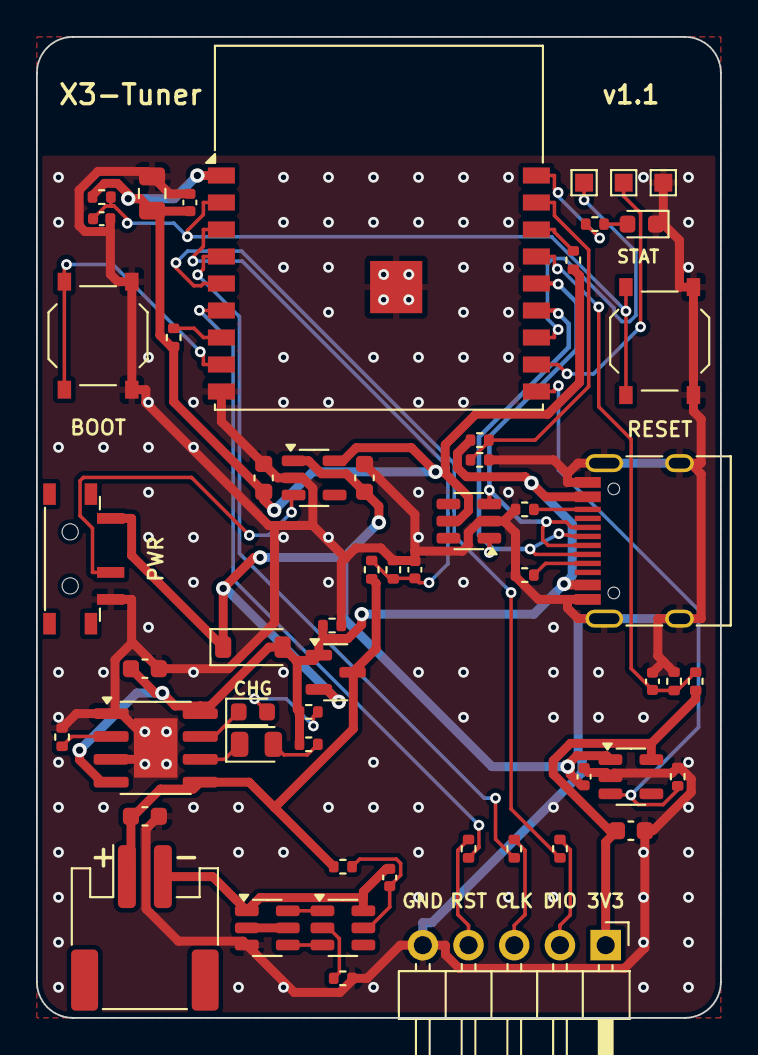
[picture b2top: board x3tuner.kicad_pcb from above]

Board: 2 copper layers, 38.0 x 54.5 mm, 61 parts (0 on the bottom side), 40 nets.

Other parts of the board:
KT1, KT2, KT3, KT4, KT5, KT6: Tab

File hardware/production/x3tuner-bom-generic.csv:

Designator,Qty,Value,Package,Manufacturer,MPN,LCSC,Description
C1,1,22uF,C_0805_2012Metric,,,C45783,"MLCC X5R/X7R, >= 10 V"
"C2,C6,C11,C12",4,100nF,C_0402_1005Metric,,,C1525,"MLCC X5R/X7R, >= 10 V"
"C3,C9",2,1uF,C_0402_1005Metric,,,C52923,"MLCC X5R/X7R, >= 10 V"
"C4,C5,C7,C8,C10",5,10uF,C_0603_1608Metric,,,C19702,"MLCC X5R/X7R, >= 10 V"
D1,1,B5819W,D_SOD-123,CJ,B5819W SL,C8598,Power-Path USB → System
D2,1,red,LED_0603_1608Metric,KENTO,KT-0603R,C2286,LED rot = lädt
D3,1,green,LED_0805_2012Metric,,,C2297,LED grün = voll
D4,1,white,LED_0603_1608Metric,KENTO,KT-0603W,C2290,Status-LED weiß
J1,1,USB-C,USB_C_Receptacle_HRO_TYPE-C-31-M-12,HRO,TYPE-C-31-M-12,C165948,USB-C Buchse 16 Pin
J2,1,AKKU,JST_PH_S2B-PH-SM4-TB_1x02-1MP_P2.00mm_Horizontal,JST,S2B-PH-SM4-TB(LF)(SN),C295747,LiPo 1S Anschluss JST-PH 2.0
J3,1,SWD-ZIEL,PinHeader_1x05_P2.54mm_Horizontal,hanxia,"HX PZ2.54-1x5P WZ (1x5 2.54 mm, gewinkelt, THT)",C32713264,Stiftleiste 1x5 gewinkelt zum Scooter (3V3 DIO CLK RST GND)
Q1,1,AO3401A,SOT-23,AOS,AO3401A,C15127,Power-Path Akku → System (P-MOSFET)
Q2,1,HJ8205,SOT-23-6,HJ,"HJ8205 (alt. FS8205A SOT-23-6, same pinout)",C20069150,Dual N-MOSFET Akku-Schutz
"R1,R2",2,5.1k,R_0402_1005Metric,,,C25905,"Widerstand 1 %, Dickschicht"
"R3,R21,R22",3,10k,R_0402_1005Metric,,,C25744,"Widerstand 1 %, Dickschicht"
R4,1,3.3k,R_0402_1005Metric,,,C25890,"Widerstand 1 %, Dickschicht"
"R5,R6,R9",3,1k,R_0402_1005Metric,,,C11702,"Widerstand 1 %, Dickschicht"
"R7,R10,R14,R15,R16,R17,R18,R19",8,100k,R_0402_1005Metric,,,C25741,"Widerstand 1 %, Dickschicht"
"R8,R11,R12,R13,R20",5,100,R_0402_1005Metric,,,C25076,"Widerstand 1 %, Dickschicht"
SW1,1,EIN/AUS,SW_SPDT_MSK12C02,SHOU HAN,MSK12C02,C431540,Schiebeschalter Ein/Aus
SW2,1,RESET,SW_Push_1P1T_XKB_TS-1187A,XKB,TS-1187A-B-A-B,C318884,Taster RESET
SW3,1,BOOT,SW_Push_1P1T_XKB_TS-1187A,XKB,TS-1187A-B-A-B,C318884,Taster BOOT / Funktion
U1,1,ESP32-C3-WROOM-02-N4,ESP32-C3-WROOM-02_JLC,Espressif,ESP32-C3-WROOM-02-N4,C2934560,"ESP32-C3, 4 MB Flash, 400 KB SRAM, WiFi + BLE"
U2,1,TP4056,SOIC-8-1EP_3.9x4.9mm_P1.27mm_EP2.41x3.3mm,TOPPOWER,TP4056-42-ESOP8,C16581,"Li-Ion Lader 1S, ~360 mA"
U3,1,DW01A,SOT-23-6,PUOLOP,DW01A,C351410,Akku-Schutz IC
"U4,U5",2,ME6211C33M5G-N,SOT-23-5,Microne,ME6211C33M5G-N,C82942,"LDO 3,3 V ESP32 (500 mA)"
U6,1,SRV05-4,SOT-23-6,TECH PUBLIC,"SRV05-4 (alt. ProTek SRV05-4-P-T7, same pinout)",C558418,USB ESD-Schutz

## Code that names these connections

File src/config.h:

// x3utils-esp32 — build-time configuration.
//
// Pins, WiFi defaults, and SWD timing live here so a user only edits one file.
// Every value can also be changed at runtime from the web UI (Settings panel);
// the values here are the power-on defaults.

#pragma once

#include <Arduino.h>

// ── SWD wiring ───────────────────────────────────────────────────────────────
// Connect these ESP32 GPIOs to the VCU debug header:
//   SWCLK  -> chip SWCLK
//   SWDIO  -> chip SWDIO
//   NRST   -> chip nRST / C45 (optional but strongly recommended)
//   GND    -> common ground (ALWAYS)
//
// Use 3.3 V logic only. Power the VCU from ONE source at a time (main/bench
// power OR the ESP32 3V3 pin) exactly as the upstream x3utils wiki warns.
#if defined(X3_BOARD_TUNER)
// X3-Tuner PCB (hardware/, ESP32-C3-WROOM-02): the SWD trio is on the
// module's left pads, closest to the target header.
static const int PIN_SWCLK_DEFAULT = 5;
static const int PIN_SWDIO_DEFAULT = 6;
static const int PIN_NRST_DEFAULT = 7;
static const int PIN_LED_DEFAULT = 0;
#elif defined(X3_BOARD_C3) || defined(X3_BOARD_CARRIER)
// Plain ESP32-C3 SuperMini, also on the X3-Tuner Mini carrier (hardware/carrier/)
static const int PIN_SWCLK_DEFAULT = 4;
static const int PIN_SWDIO_DEFAULT = 5;
static const int PIN_NRST_DEFAULT = 6;
static const int PIN_LED_DEFAULT = 8;
#elif defined(X3_BOARD_S3)
static const int PIN_SWCLK_DEFAULT = 4;
static const int PIN_SWDIO_DEFAULT = 5;
static const int PIN_NRST_DEFAULT = 6;
static const int PIN_LED_DEFAULT = 48;
#else  // classic ESP32
static const int PIN_SWCLK_DEFAULT = 18;
static const int PIN_SWDIO_DEFAULT = 19;
static const int PIN_NRST_DEFAULT = 21;
static const int PIN_LED_DEFAULT = 2;
#endif

// ── X3-Tuner board extras ────────────────────────────────────────────────────
// Only the X3-Tuner PCB has these; on dev boards they are -1 and the matching
// features (battery gauge, switchable target supply) simply report "absent".
#if defined(X3_BOARD_TUNER)
static const int PIN_TGT_EN = 10;      // high = target LDO (3.3 V to the VCU) on
static const int PIN_VTGT_SENSE = 3;   // ADC1: VTGT through a 1:2 divider
static const int PIN_VBAT_SENSE = 4;   // ADC1: battery through a 1:2 divider
static const int PIN_VBUS_SENSE = 1;   // ADC1: VBUS through a 1:2 divider (USB present)
#elif defined(X3_BOARD_CARRIER)
// X3-Tuner Mini carrier with a plug-in ESP32-C3 SuperMini (hardware/carrier/)
static const int PIN_TGT_EN = 7;       // low = target supply on (P-MOSFET gate)
static const int PIN_VTGT_SENSE = 3;   // ADC1: VTGT through a 1:2 divider
static const int PIN_VBAT_SENSE = 0;   // ADC1: battery through a 1:2 divider (1M/1M)
static const int PIN_VBUS_SENSE = 1;   // ADC1: SuperMini 5V pin through a 1:2 divider
#else
static const int PIN_TGT_EN = -1;
static const int PIN_VTGT_SENSE = -1;
static const int PIN_VBAT_SENSE = -1;
static const int PIN_VBUS_SENSE = -1;
#endif

#if defined(X3_BOARD_CARRIER)
static const int TGT_EN_ON = LOW;      // P-MOSFET straight from the GPIO
static const int LED_ON = LOW;         // SuperMini LED is wired to 3V3
// On battery the 5V pin still sees the cell minus a Schottky drop (<= 3.9 V),
// so USB is only assumed above 4.3 V.
static const int VBUS_PRESENT_MV = 4300;
#else
static const int TGT_EN_ON = HIGH;
static const int LED_ON = HIGH;
static const int VBUS_PRESENT_MV = 3500;
#endif

// A VCU already showing more than this on its 3V3 pin is powered from
// somewhere else; the board then refuses to switch its own supply on.
static const int TARGET_EXTERNAL_MV = 1000;

// Half-clock delay for the bit-banged SWD line, in microseconds. 0 lets the
// line run as fast as the GPIO API allows (a few hundred kHz on a classic
// ESP32), which is reliable for short cables. Raise to 1–3 if a long or noisy
// cable throws "SWD: no ACK" / parity errors.
static const uint8_t SWD_HALF_CLOCK_US_DEFAULT = 0;

// ── WiFi ─────────────────────────────────────────────────────────────────────
// Default is a self-hosted access point so the iPhone just joins the ESP32's
// own network — no router, no internet. Connect to this SSID, then open
// http://192.168.4.1/ in Safari (or any browser).
//
// You can instead join an existing WiFi from the Settings panel; the choice is
// stored in flash and used on the next boot.
static const char AP_SSID_DEFAULT[] = "x3utils-esp32";
static const char AP_PASSWORD_DEFAULT[] = "x3utils123";  // >= 8 chars, or "" for open
static const char MDNS_HOSTNAME[] = "x3utils";           // http://x3utils.local/

// ── Target geometry (AT32F415, 128 KB) ───────────────────────────────────────
static const uint32_t FLASH_BASE = 0x08000000UL;
static const uint32_t SLOT0_BASE = 0x08001000UL;
static const uint32_t BACKUP_LENGTH = 131072UL;  // 128 KB — the only backup size
